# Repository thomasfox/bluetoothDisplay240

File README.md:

# bluetoothDisplay240

A bluetooth display for displaying speed, direction and a direction deviation bar while sailing.
Speed, direction and direction deviation measurements are transmitted via bluetooth, 
e.g. by a smartphone. The sum of component prices is about 100€.

This project contains
- The PCB and schematic of the circuit board in the [hardware](hardware) directory
- The code for the arduino compatible microcontroller on the circuit board in the [software](software) directory
- a Housing for 3D Printing  in the [housing](housing) directory
  (alternatively, you can use a commercial housing)

At the time of writing, material costs were approximately 100€. 
The electronics runs with 3.3V supply voltage, so it can be operated using a single LI-Ion battery.
The electronics draws about 15 mA supply current, so that with a 800 mAH battery, 
operation time is more than 50h without reloading.

## Electronics

The main components of the ectronics are an arduino-compatible microcontroller board,
a graphical LCD Display with 240x64 pixels, and a Bluetooth Low Energy board. 
Discrete components are used for a soft-power latch and a battery watchdog. 

The quiescent current while being switched off is less than 1 μA,
so the standby-time for a 800 mA battery is only limited by the self-discharge time
of the battery.

The LCD display can be plugged in via socket rows. 
In my experience, not all socker rows provide a good contact to the LCD Display,
I had better experiences with the cheaper ones.

The arduino compatible board is soldered on using post rows, so that there is a small gap 
between the PCB and the arduino compatible board.

The press-button switch should only provide contact while pressed.
If a waterproof housing is wanted, the switch should be at least IP67 classed.

The battery charging circuit board in the BOM provides 1A of charging current.
I prefer a lower charging current of 250 mA, for which the R3 Resistor 
on the charging circuit board must be replaced by a 4k7 SMD resistor.
The charging PCB and the Arduino compatible board both use their own micro USB socket;
note that charging is not possible using the Arduino-compatible board USB socket, 
and programming is not possible using the charging board USB socket.

The current PCB design has a small flaw because the large foil condensators must lie on the PCB
rather than stand; but there is no explicit place reserved for that. 
So these condensators must be laid on top of other components, which worked for me.

The components needed are listed in the [Bill of Material (BOM)](hardware/bom.md). 
I obtained most of the components from the distributor [Reichelt](https://www.reichelt.de).
For your convenience, I have a public list there 
[https://www.reichelt.de/my/1939286](https://www.reichelt.de/my/1939286) 
containing the components marked in the BOM.
The HM 17 Bluetooth module was obtained from an ebay shop,
the non-marked resistors from a resistor assortment and the litz wire also from Reichelt.
Feel free to purchase the components where you want,
I do not earn anything if you purchase from Reichelt!

Then you need the PCB, I had mine made by [Aisler](https://aisler.net/), but again feel free to use another manufacturer.

Approximate prices at the time of writing were

| **Item**      | **material** | **shipping** |
| ------------- | ------------ | ------------ |
| Reichelt List | 70€          | 6€           |
| HM17          | 11€          | 3€           |
| PCB           | 13€ for a batch of 3 | -    |

which adds up to about 100€ for one display.

### Assembly

You need a soldering iron with a small tip and soldering lead.
There are three SMD FET's on the PCB, which can be soldered with a soldering iron.
This can be a little tricky for an inexperienced solderer like me, but it worked in the end.
I'd recommend to solder the SMD FETs at the beginning, because then there is a 
Then, the film capacitors should be soldered at the end and with as much spare wire above the PCB as possible,
because they need to be bent in order to put the LCD display on top.

The battery holder should be connected to the charging board, 
which in turn should be connected to CONN1 using litz wire.
The push-Button switch should be connected to CONN2 also using litz wire.

You can consider to lacquer the board after all is finished and tested to improve water resistance. 
Be sure not to lacquer the pin rows, the lacquer tends to creep up in the pin holes.

## Software

You need to load the software onto the arduino compatible microcontroller board, e.g. using the Arduino IDE
and a micro USB cable. Make sure to select the correct board (Adafruit Trinket 3V) 
and the correct Programmer (USBtinyISP) in the Arduino IDE.

A good test is to try and upload a simple Arduino demo program (e.g. blink) onto the board 
before it is soldered in to make sure everything works as expected.

As the USB port on the microcontroller board is software-implemented,
new USB 3.0 ports typically lead to upload errors. 
The solution in my case was to use a cheap USB 2.0 hub between the PC and the microcontroller board.

To feed the display, I use my [Saillogger](https://github.com/thomasfox/saillogger) android app.

## Bluetooth Low Energy Protocol

The bluetooth low energy (BLE) transmission protocol is very simple: 
The feeding device writes the field identifier, a colon (:) and the value of the addressed field
to the one BLE characteristic offered by the device's BLE receiver. After that, the sending device needs to wait some time
(should be some 10 ms, I still need to find out how long) before sending the next value.

The field id is f1 for the velocity field, f2 for the direction field and f3 for the direction bar.
For the f1 and f2 fields, the value can be any short string containing the characters a-z, A-Z, 0-9 or .,:
(short meaning the value fits in the field's window in the display).
For the f3 field, the value needs to be an integer value between -100 and 100.
The character ';' should act as a field separator (I need to verify whether that works).

For the used characteristic, the service uuid is "0000ffe0-0000-1000-8000-00805f9b34fb"
and the characteristic uuid is "0000ffe1-0000-1000-8000-00805f9b34fb"

You can use  [Saillogger's BLE sender](https://github.com/thomasfox/saillogger/blob/master/app/src/main/java/com/github/thomasfox/saildata/sender/BleSender.java)
as a java/android code example for a bluetooth sender.

## Housing

The Housing consists of the main housing, a lid which is glued to the main housing, 
and a screw-lid through which the two USB sockets can be accessed. 
They can be 3D printed, I used PLA as printing material.

For a waterproof screw-lid, an o-ring is needed with an inner diameter of 20mm 
and a material diameter of 2mm.

The LCD Display is glued in the main housing, such that no water can enter between housing and Display.
Then the charging board is glued into the tube of the screw-lid, and the switch and battery holder 
are also glued into place.
Then the circuit board is connected to the LCD display, and the lid is glued an, 
also in such a way that no water can enter.

For gluing, I used pattex repair glue, which is transparent and stays flexible when cured, but any similar glue will do.

## Alternative Housing

I had some difficulties in getting my own housing really waterproof, so as an alternative
you can use a commercial housing. I used the 130x80x35mm FIBOX PC 100/35 LT Housing, 
which was available at the time of writing for €17 plus 5€ shipping from [Conrad](https://www.conrad.de).
The LCD needs to be glued to the transparent cover; I glued just the edges. 
Also a hole needs to be drilled for the push-button switch, which then also needs to be glued in.

## Questions?

Please open a [issue](../../issues) if you have any questions.

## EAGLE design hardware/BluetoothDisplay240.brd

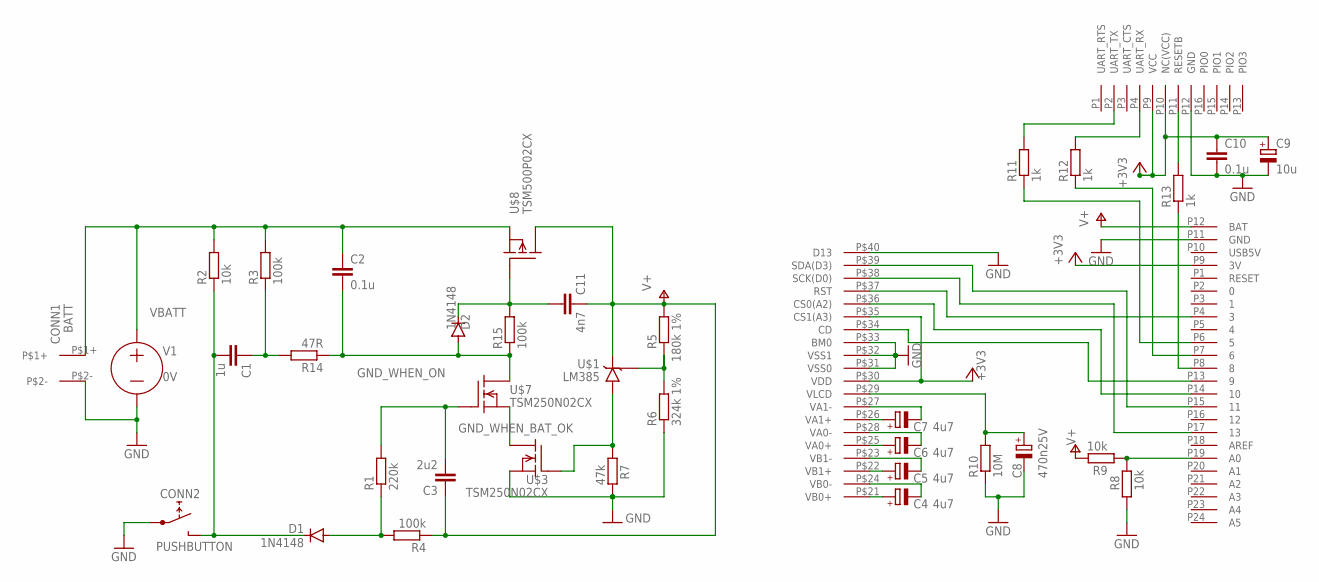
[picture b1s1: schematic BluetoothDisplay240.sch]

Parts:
C1: 1u; C025-060X050
C2: 0.1u; C025-030X050
C3: 2u2; C075-063X106
C4, C5, C6, C7: 4u7; B45181A
C8: 470n25V; B45181A
C9: 10u; B45181A
C10: 0.1u; C025-025X050
C11: 4n7; C025-030X050
CONN1: BATT; 2-PIN_CONN
CONN2: PUSHBUTTON; 2-PIN_CONN
D1, D2: 1N4148; DO35-7
R1: 220k; 0207/10
R2, R8, R9: 10k; 0207/10
R3, R4, R15: 100k; 0207/10
R5: 180k 1%; 0207/10
R6: 324k 1%; 0207/10
R7: 47k; 0207/10
R10: 10M; 0207/10
R11, R12, R13: 1k; 0207/10
R14: 47R; 0207/10
U$1: LM385; TO92.PAC
U$3, U$7: TSM250N02CX; SOT23
U$4: DOGM240-6; LCD-DISPLAY
U$5: TRINKET3V
U$6: HM-17
U$8: TSM500P02CX; SOT23

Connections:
+3V3: C9.+, C10.1, U$4.P$30 (VDD), U$4.P$35 (CS1(A3)), U$5.P9 (3V), U$6.P9 (VCC), U$6.P10 (NC(VCC))
BT_RES: R13.2, U$6.P11 (RESETB)
BT_RES1: R13.1, U$5.P8 (8)
BT_RX: R12.2, U$6.P4 (UART_RX)
BT_RX1: R12.1, U$5.P7 (6)
BT_TX: R11.2, U$6.P2 (UART_TX)
BT_TX1: R11.1, U$5.P6 (5)
CD_DISP: U$4.P$34 (CD), U$5.P13 (9)
CS_DISP: U$4.P$36 (CS0(A2)), U$5.P14 (10)
GND: C8.-, C9.-, C10.2, CONN1.P$2-, CONN2.P$1+ (1A), R6.1, R7.2, R8.1, R10.1, U$3.2 (S), U$4.P$31 (VSS0), U$4.P$32 (VSS1), U$4.P$33 (BM0), U$4.P$40 (D13), U$5.P11 (GND), U$6.P12 (GND)
GND_WHEN_BAT_OK: U$3.3 (D), U$7.2 (S)
GND_WHEN_ON: C2.2, D2.A, R14.1, R15.1, U$7.3 (D)
HIGH_WHEN_BAT_OK: R7.1, U$1.1 (GND), U$3.1 (G)
unnamed: C4.+, U$4.P$21 (VB0+)
unnamed: C1.1, R3.1, R14.2
unnamed: C4.-, U$4.P$24 (VB0-)
unnamed: C5.+, U$4.P$22 (VB1+)
unnamed: C5.-, U$4.P$23 (VB1-)
unnamed: C6.+, U$4.P$25 (VA0+)
unnamed: C6.-, U$4.P$28 (VA0-)
unnamed: C7.+, U$4.P$26 (VA1+)
unnamed: C7.-, U$4.P$27 (VA1-)
ON_CTL: C11.2, D2.C, R15.2, U$8.1 (G)
PUSH_GND: C1.2, CONN2.P$2- (A2), D1.C, R2.1
PUSH_GND_2: D1.A, R1.1, R4.2
RST_DISP: U$4.P$37 (RST), U$5.P4 (3)
SCK_DISP: U$4.P$38 (SCK(D0)), U$5.P17 (13)
SDA_DISP: U$4.P$39 (SDA(D3)), U$5.P15 (11)
SWITCH_STATE: C3.2, R1.2, U$7.1 (G)
V+: C3.1, C11.1, R4.1, R5.2, R9.2, U$1.2 (VOUT), U$5.P12 (BAT), U$8.3 (D)
V+LOW_SENSE: R5.1, R6.2, U$1.3 (REF)
V+_SENSE: R8.2, R9.1, U$5.P19 (A0)
VBATT: C2.1, CONN1.P$1+, R2.2, R3.2, U$8.2 (S)
VLCD: C8.+, R10.2, U$4.P$29 (VLCD)

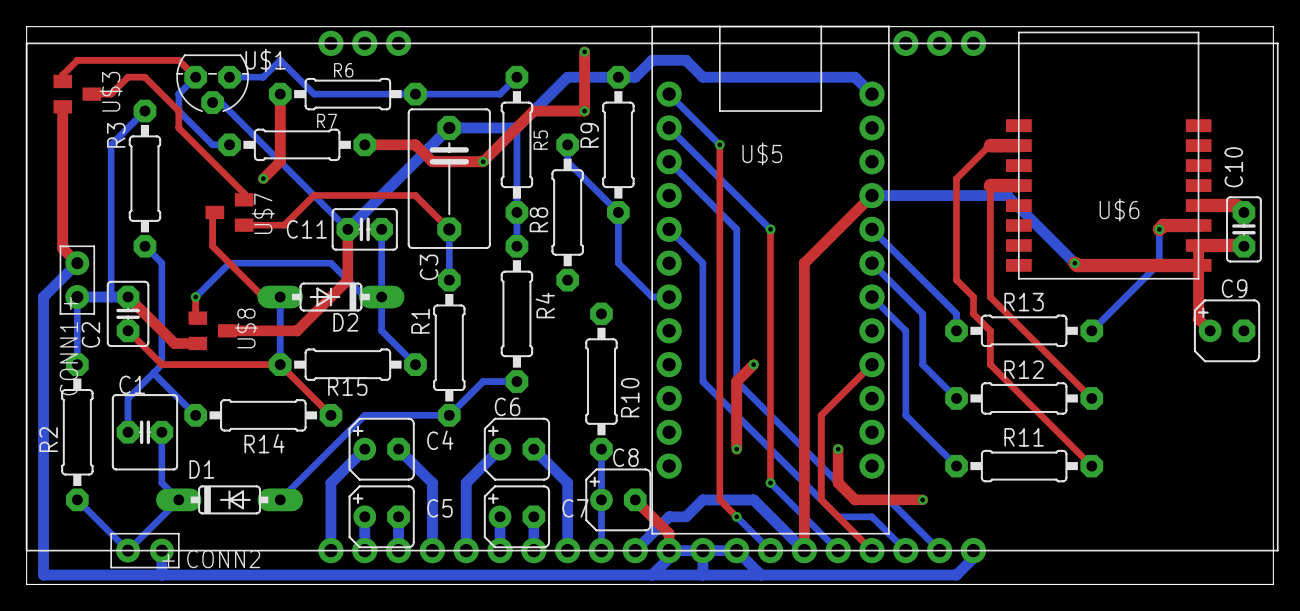
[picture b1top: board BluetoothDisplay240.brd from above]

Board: 2 copper layers, 93.7 x 41.9 mm, 37 parts (0 on the bottom side), 34 nets.

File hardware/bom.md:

| **Quantity** | **Value** | **Additional Info**  | **Name** | **Contained in Reichelt List** |
| -------------| --------- | -------------------- | -------- | ------------------------------ |
| **Condensators** |
| 1            | 4n7       | 10V Ceramic          | C11      | x |
| 2            | 0.1u      | 10V Film             | C2,C10   | x |
| 1            | 470n      | 25V Tantal           | C8       | x |
| 1            | 1u        | 10V Film             | C1       | x |
| 1            | 2.2u      | 10V Film             | C3       | x |
| 4            | 4.7u      | 10V Tantal           | C4,C5,C6,C7 | x |
| 1            | 10u       | 10V Tantal           | C9       | x |
| **Diodes**   |
| 2            | 1N4148    |                      | D1,D2    | x |
| **Resisitors** |
| 1            | 47R       | 1/4W 5%              | R14      |   |
| 3            | 1k        | 1/4W 5%              | R11,R12,R13 | |
| 3            | 10k       | 1/4W 5%              | R2,R8,R9 |   |
| 1            | 47k       | 1/4W 5%              | R7       |   |
| 3            | 100k      | 1/4W 5%              | R3,R4,R15 |  |
| 1            | 220k      | 1/4W 5%              | R1       |   |
| 1            | 180k      | 1/4W 1%              | R5       | x |
| 1            | 324k      | 1/4W 1%              | R6       | x |
| 1            | 10M       | 1/4W 5%              | R10      | x |
| **Other**    |
| 1            |           | LM385Z               | U$1      | x |
| 2            |           | TSM250N02CX or TSM2302SMD | U$3, U$7 | x |
| 1            |           | TSM500P02CX          | U$8      | x |
| 1            |           | DOGM240-6            | U$4      | x |
| 1            |           | TRINKET3V            | U$5      | x |
| 1            |           | HM-17 Bluetooth Module | U$6    |   |
| 1            |           | Press-Button switch  |          | x |
| **Charger Board** |
| 1            |           | DEBO2 3.7LI 1.0A     |          | x |
| 1            | 4k7       | SMD Resistor 0603 100mW |       | x |
| **Battery & Battery holder** |
| 1            |           | Li-Ion Battery 3,7V  |          | x |
| 1            |           | Battery Holder       |          | x |
| **Socket rows** |
| 1            |           | 20-Pin row 2,54mm    |          | x |
| 2            |           | 3-Pin row 2,54mm     |          | x |
| **Pin rows (probably contained in Trinket3V)**  |
| 1            |            | 7-pin 1row 2,54mm   |          | x |
| 1            |            | 12-pin 1row 2,54mm  |          | x |
| **wire**   |
| 6            |            | 15 cm litz wire     |          |   |

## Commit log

2022-07-10 version 1.0.0 hardware and software
2022-07-10 add questions chapter to readme
2022-09-04 add BLE protocol info to README
2022-09-04 small wording corrections
2022-09-14 fix typo
2022-09-24 correct battery scale; display overflowing incomplete BLE buffer
